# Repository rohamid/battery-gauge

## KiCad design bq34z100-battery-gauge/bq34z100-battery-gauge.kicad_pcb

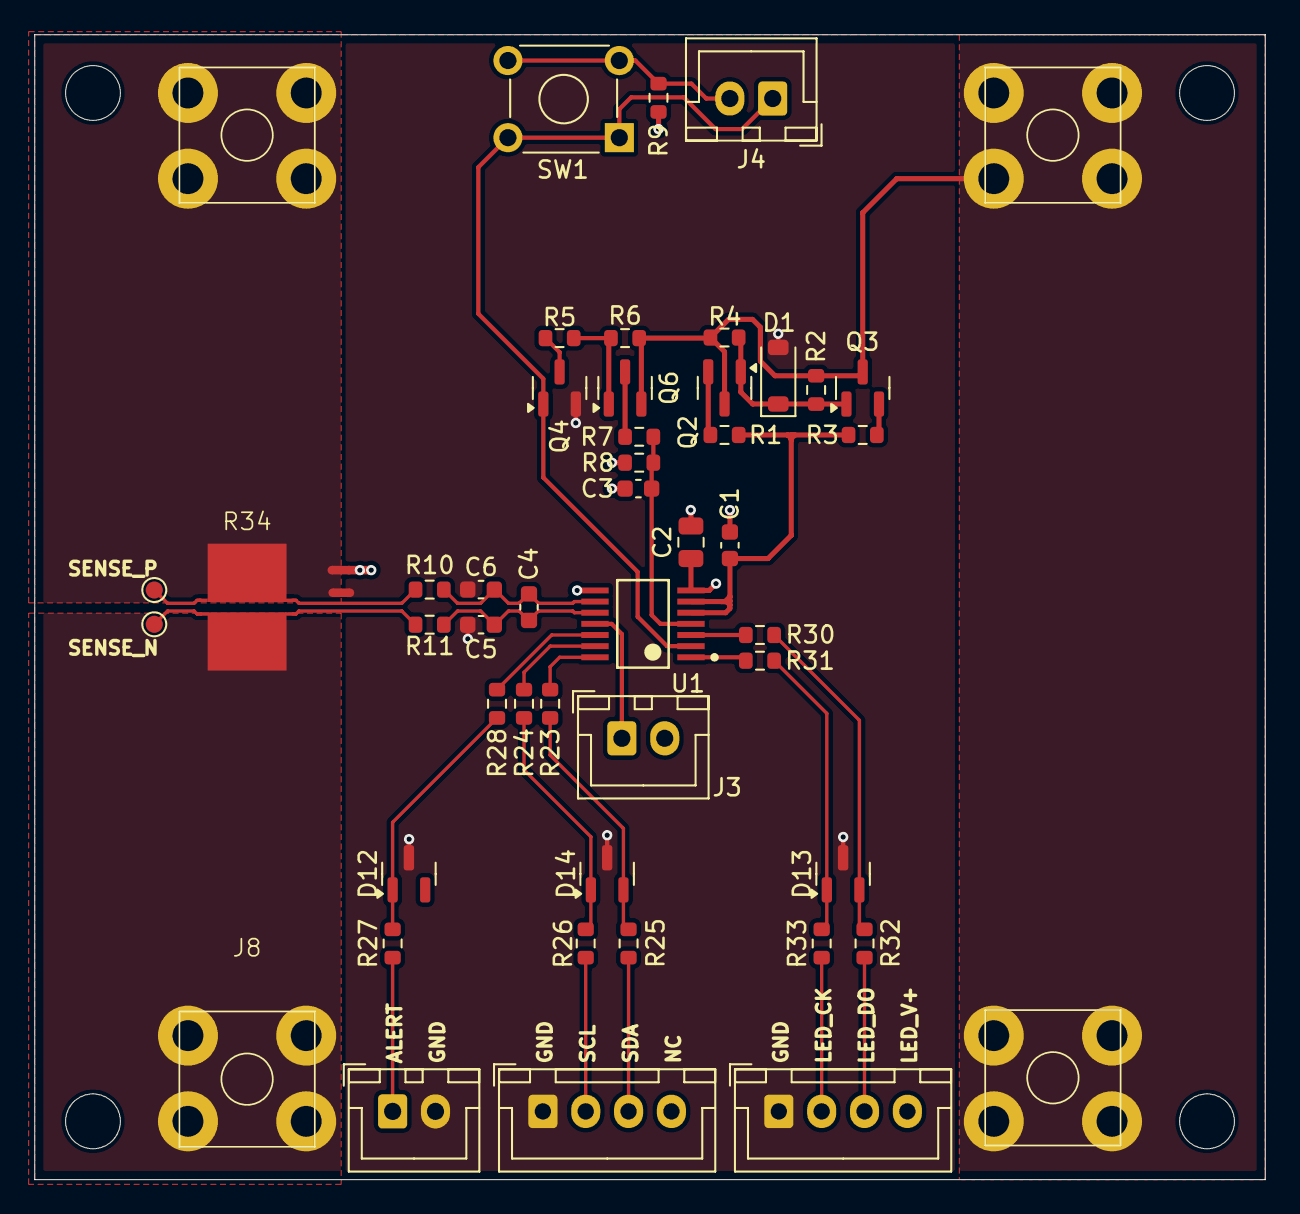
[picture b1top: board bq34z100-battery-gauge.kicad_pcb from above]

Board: 4 copper layers, 71.8 x 66.8 mm, 55 parts (0 on the bottom side), 36 nets.

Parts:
C1, C4, C5, C6: 100nF; C_0603_1608Metric
C2: 1uF; C_0805_2012Metric
C3: 3300pF; C_0603_1608Metric
D1: 5V6; D_SOD-123
D12, D13, D14: AZ23C5V6-7; SOT-23
H1, H2, H3, H4: MountingHole; MountingHole_3.2mm_M3
J1: Conn_01x04; JST_XH_B4B-XH-A_1x04_P2.50mm_Vertical
J2: ALERT; JST_XH_B2B-XH-A_1x02_P2.50mm_Vertical
J3: NTC; JST_XH_B2B-XH-A_1x02_P2.50mm_Vertical
J4: LED_DISP; JST_XH_B2B-XH-A_1x02_P2.50mm_Vertical
J5, J6: BAT; square_terminal
J7, J8: LOAD; square_terminal
J11: LED; JST_XH_B4B-XH-A_1x04_P2.50mm_Vertical
NT2, NT3: NetTie_2; NetTie-2_SMD_Pad0.5mm
Q2, Q3: 2N7002; SOT-23
Q4: BSS138; SOT-23
Q6: BSS84; SOT-23
R1, R3: 47; R_0603_1608Metric
R2, R4: 27K; R_0603_1608Metric
R5: 165K; R_0603_1608Metric
R6: 100K; R_0603_1608Metric
R7: 300K/0.1%; R_0603_1608Metric
R8: 165K/0.1%; R_0603_1608Metric
R9: 1K; R_0603_1608Metric
R10, R11, R23, R24, R25, R26, R27, R28, R30, R31, R32, R33: 100; R_0603_1608Metric
R34: 0.01; Isabellenhuette-SMT-R010-1.0
SW1: LED_SW; SW_TH_Tactile_Omron_B3F-10xx
TP1, TP2: TestPoint; TestPoint_Pad_D1.0mm
U1: BQ34Z100PWR-G1; Texas_Instruments-PW0014A-0-0-0

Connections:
/LED_CLK: R31.2, U1.1 (P2)
/LED_DAT: R30.2, U1.3 (P1)
/LED_SW: J4.2, R9.2, SW1.2
/REG25: C2.1, J3.2, R9.1, U1.7 (REG25)
/SENSE_N: R11.1, R34.3, TP2.1
/SENSE_P: R10.1, R34.2, TP1.1
/SRN: C4.2, C5.1, R11.2, U1.10 (SRN)
/SRP: C4.1, C6.1, R10.2, U1.9 (SRP)
/VEN: J4.1, Q4.1 (G), SW1.1, U1.2 (VEN)
GND: C5.2, C6.2, D1.2 (A), D12.3 (A), D13.3 (A), D14.3 (A), J1.1, J2.2, J11.1, NT2.1, Q4.2 (S)
GNDA: C1.2, C2.2, C3.2, NT3.1, R8.1, U1.8 (VSS)
unnamed: D1.1 (K), Q2.1 (G), Q3.1 (G), R2.2, R4.2
unnamed: D12.1 (K), R27.2, R28.1
unnamed: D13.1 (K), R31.1, R33.2
unnamed: D13.2 (K), R30.1, R32.2
unnamed: D14.1 (K), R24.1, R26.2
unnamed: D14.2 (K), R23.1, R25.2
unnamed: J1.2, R26.1
unnamed: J1.3, R25.1
unnamed: J2.1, R27.1
unnamed: J3.1, U1.11 (P6/TS)
unnamed: J11.2, R33.1
unnamed: J11.3, R32.1
unnamed: Q2.2 (S), R1.2
unnamed: Q3.2 (S), R3.2
unnamed: Q4.3 (D), R5.1
unnamed: Q6.3 (D), R7.2
unnamed: Q6.1 (G), R5.2, R6.1
unnamed: C3.1, R7.1, R8.2, U1.4 (BAT)
unnamed: R23.2, U1.14 (P3/SDA)
unnamed: R24.2, U1.13 (P4/SCL)
unnamed: R28.2, U1.12 (P5/HDQ)
PACK-: J8.1, R34.4
REGIN: C1.1, R1.1, R3.1, U1.5 (CE), U1.6 (REGIN)
VBAT+: J5.1, J7.1, Q2.3 (D), Q3.3 (D), Q6.2 (S), R2.1, R4.1, R6.2
VBAT-: J6.1, NT2.2, NT3.2, R34.1

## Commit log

2025-01-22 relocate doc folder
2025-01-23 Change Resistor to issabelenhurt, change mounting hole dimension
2025-01-24 1. Finished tracks, (need to verify grounding layer below battery tracks). 2. Added more literature document
